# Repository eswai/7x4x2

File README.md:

# 7x4x2 - wireless split ortholinear keyboard

7x4x2 (seven-four-two)はBluetooth対応の左右分割式、格子配列のキーボードです。
本キーボードはSatT氏が設計されたCaravelleの公開情報を活用させていただき、主にキーの配列を変更したものです。
SatT氏のご厚意に感謝いたします。

## 必要な部品

- タカチ電機工業 BK型コイン電池ホルダー BK-869
- 電池 CR1632
- マイコン Laird BL652-SA-01-T/R 
- チップ積層セラミックコンデンサー 100μF6.3V X6R 3216
- チップ積層セラミックコンデンサー 0.1μF50V F 2012
- 表面実装用ショットキーバリアダイオード (40V2A)SS2040FL
- 小型スライドスイッチ 1回路2接点(面実装タイプ)  SSW1P2T-SMT
- アルプス電気 (ALPS) 表面実装タクトスイッチ 5.2mm角薄型タイプ SKQGAFE010
- スタンドオフ M2 6.5mm ARB-2006.5E　
- ネジ M2x5mm
- Cherry MXスイッチ
- MXスイッチ用ソケット

## ファームウェア

1. ST-LinkとopenOCDを使用してcaravelleのブートローダーを書き込む
2. QMKファームウェアをコンパイルする https://github.com/eswai/qmk_ble/tree/nrf52/keyboards/eswai/7x4x2
3. nRF toolboxを使用して、ファームウェアを書き込む

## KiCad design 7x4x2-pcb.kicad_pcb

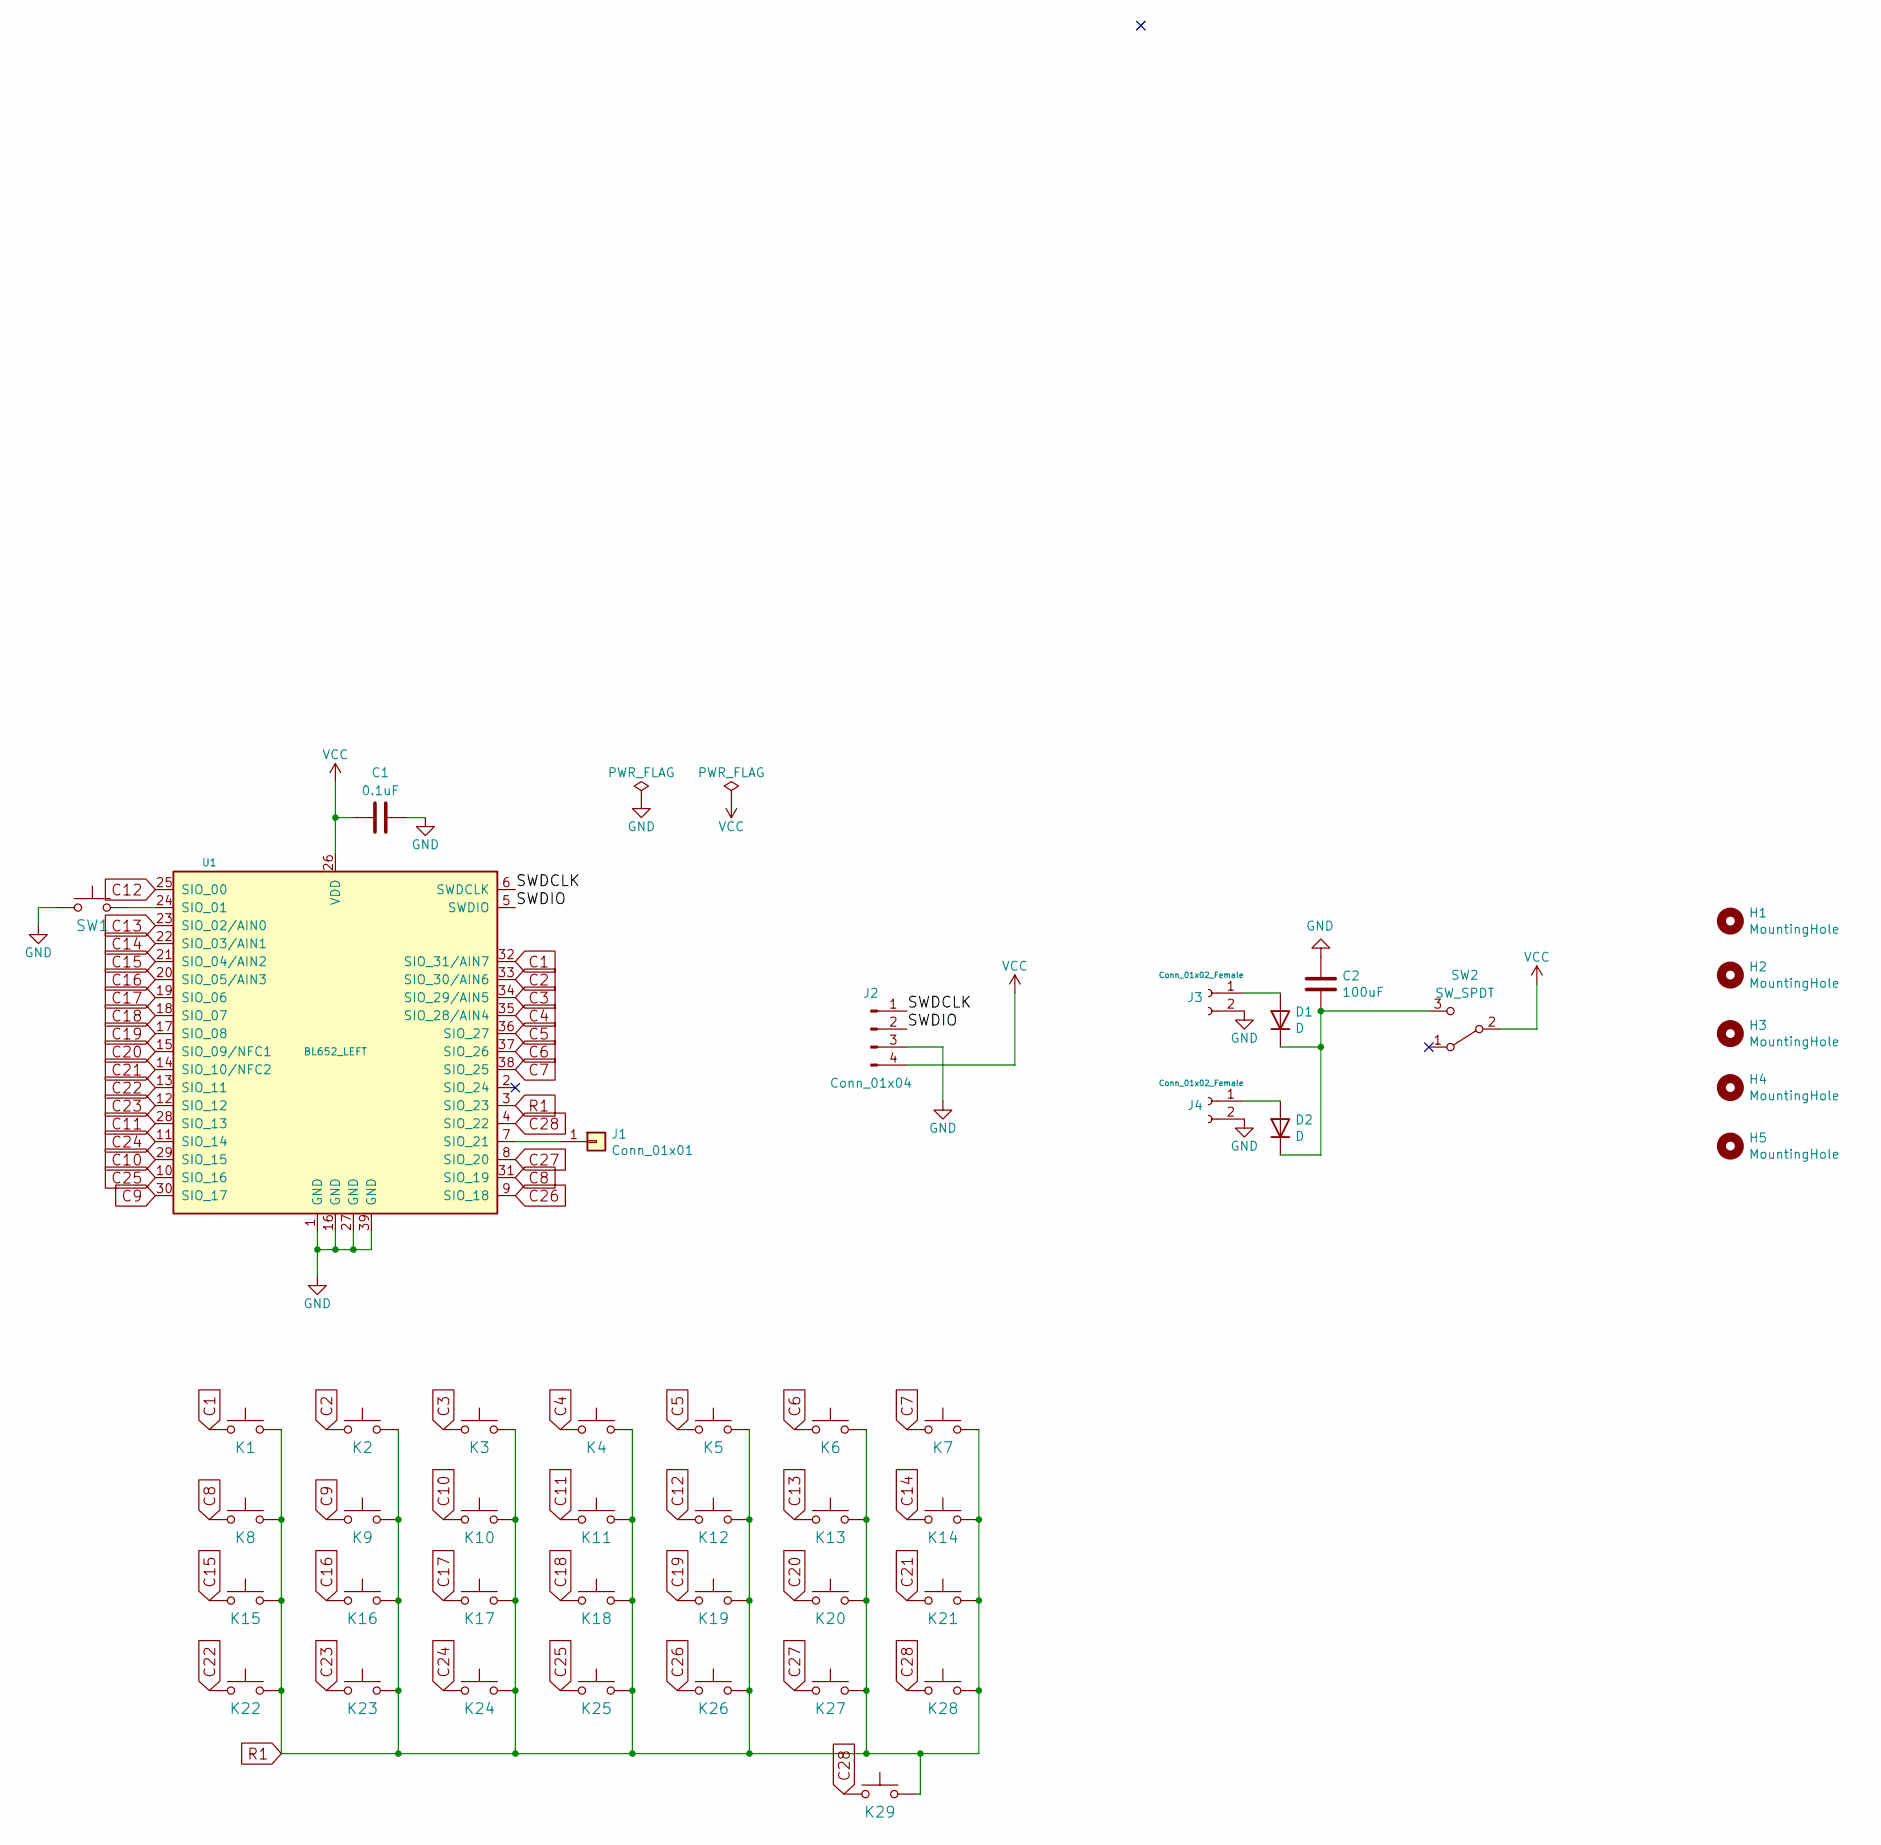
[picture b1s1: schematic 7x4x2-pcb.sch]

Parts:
C1: 0.1uF; C_0603_1608Metric_Pad1.05x0.95mm_HandSolder
C2: 100uF; C_1206_3216Metric_Pad1.42x1.75mm_HandSolder
D1, D2: D; D_SOD-123
H1, H2, H3, H4, H5: MountingHole; MountingHole_4.3mm_M4
J1: Conn_01x01; breakout-pad
J2: Conn_01x04; programming_port
J3, J4: Conn_01x02_Female; BK-869
K1, K2, K3, K4, K5, K6, K7, K8, K9, K10, K11, K12, K13, K14, K15, K16, K17, K18, K19, K20, K21, K22, K23, K24, K25, K26, K27, K28, K29: keyboard_parts_KEYSW; CherryMX_Hotswap
SW1: RESET_SW; SW_SPST_SKQG_WithoutStem
SW2: SW_SPDT; 679-1847-1-ND‎
U1: BL652_LEFT; Laird_BL652_Hand

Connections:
/SWDCLK: J2.1, U1.6 (SWDCLK)
/SWDIO: J2.2, U1.5 (SWDIO)
C1: K1.1, U1.32 (SIO_31/AIN7)
C2: K2.1, U1.33 (SIO_30/AIN6)
C3: K3.1, U1.34 (SIO_29/AIN5)
C4: K4.1, U1.35 (SIO_28/AIN4)
C5: K5.1, U1.36 (SIO_27)
C6: K6.1, U1.37 (SIO_26)
C7: K7.1, U1.38 (SIO_25)
C8: K8.1, U1.31 (SIO_19)
C9: K9.1, U1.30 (SIO_17)
C10: K10.1, U1.29 (SIO_15)
C11: K11.1, U1.28 (SIO_13)
C12: K12.1, U1.25 (SIO_00)
C13: K13.1, U1.23 (SIO_02/AIN0)
C14: K14.1, U1.22 (SIO_03/AIN1)
C15: K15.1, U1.21 (SIO_04/AIN2)
C16: K16.1, U1.20 (SIO_05/AIN3)
C17: K17.1, U1.19 (SIO_06)
C18: K18.1, U1.18 (SIO_07)
C19: K19.1, U1.17 (SIO_08)
C20: K20.1, U1.15 (SIO_09/NFC1)
C21: K21.1, U1.14 (SIO_10/NFC2)
C22: K22.1, U1.13 (SIO_11)
C23: K23.1, U1.12 (SIO_12)
C24: K24.1, U1.11 (SIO_14)
C25: K25.1, U1.10 (SIO_16)
C26: K26.1, U1.9 (SIO_18)
C27: K27.1, U1.8 (SIO_20)
C28: K28.1, K29.1, U1.4 (SIO_22)
GND: C1.2, C2.1, J2.3, J3.2, J4.2, SW1.1, U1.1 (GND), U1.16 (GND), U1.27 (GND), U1.39 (GND)
unnamed: C2.2, D1.1 (K), D2.1 (K), SW2.3 (C)
unnamed: D1.2 (A), J3.1
unnamed: D2.2 (A), J4.1
unnamed: J1.1, U1.7 (SIO_21)
unnamed: SW1.2, U1.24 (SIO_01)
R1: K1.2, K2.2, K3.2, K4.2, K5.2, K6.2, K7.2, K8.2, K9.2, K10.2, K11.2, K12.2, K13.2, K14.2, K15.2, K16.2, K17.2, K18.2, K19.2, K20.2, K21.2, K22.2, K23.2, K24.2, K25.2, K26.2, K27.2, K28.2, K29.2, U1.3 (SIO_23)
VCC: C1.1, J2.4, SW2.2 (B), U1.26 (VDD)

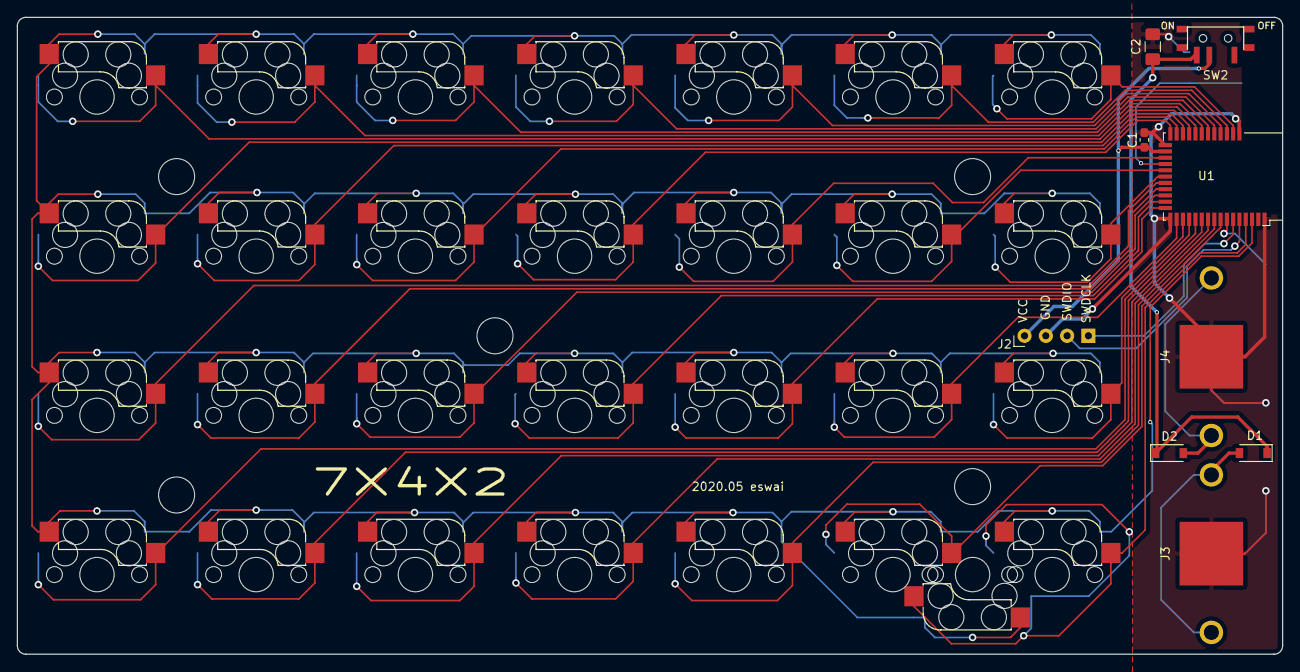
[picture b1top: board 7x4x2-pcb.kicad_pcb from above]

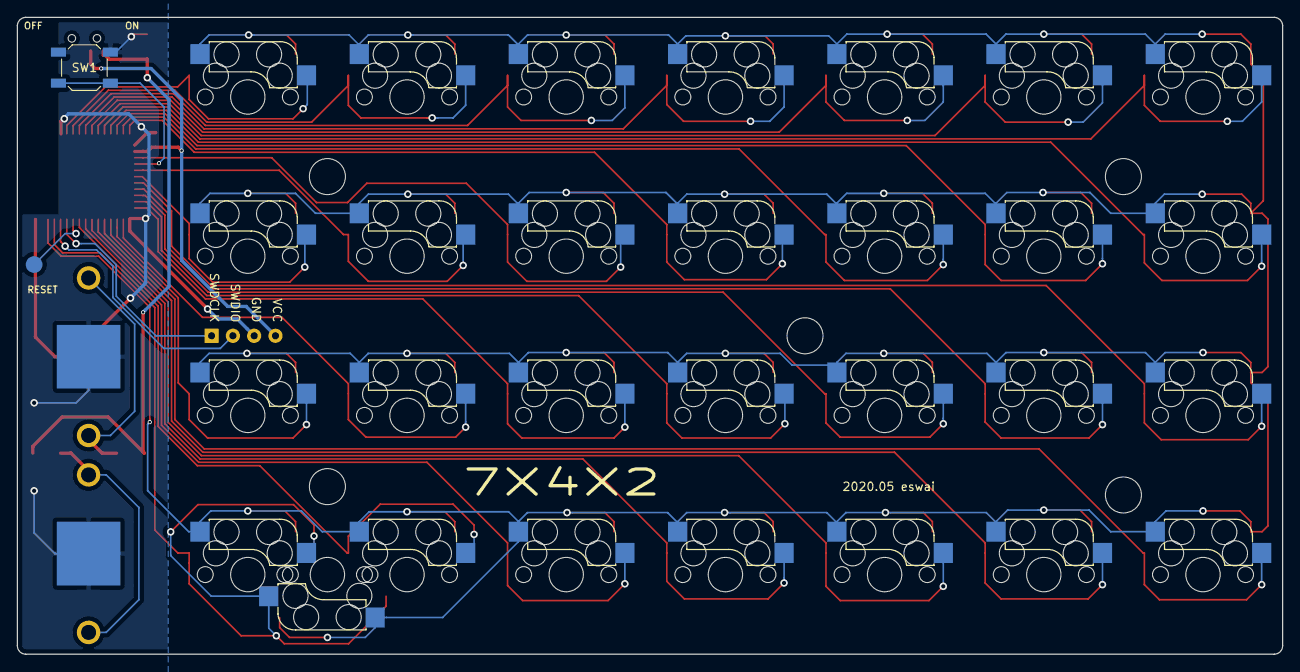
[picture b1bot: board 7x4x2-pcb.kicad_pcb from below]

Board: 2 copper layers, 151.0 x 76.0 mm, 45 parts (2 on the bottom side), 38 nets.

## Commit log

2020-05-31 unnecessary
2020-05-31 photo
